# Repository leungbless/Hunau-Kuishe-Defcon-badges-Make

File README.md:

# Hunau-Kuishe-Defcon-badges-Make
想自己制作defcon的胸卡，带破解的徽章，或者带游戏的，下载的一些资料，和学习经历和自己的总结，如果做出来，会把原件，代码开源，并且分享制作经历，欢迎大家提交分支，来帮助我们改进我们的第一个徽章。

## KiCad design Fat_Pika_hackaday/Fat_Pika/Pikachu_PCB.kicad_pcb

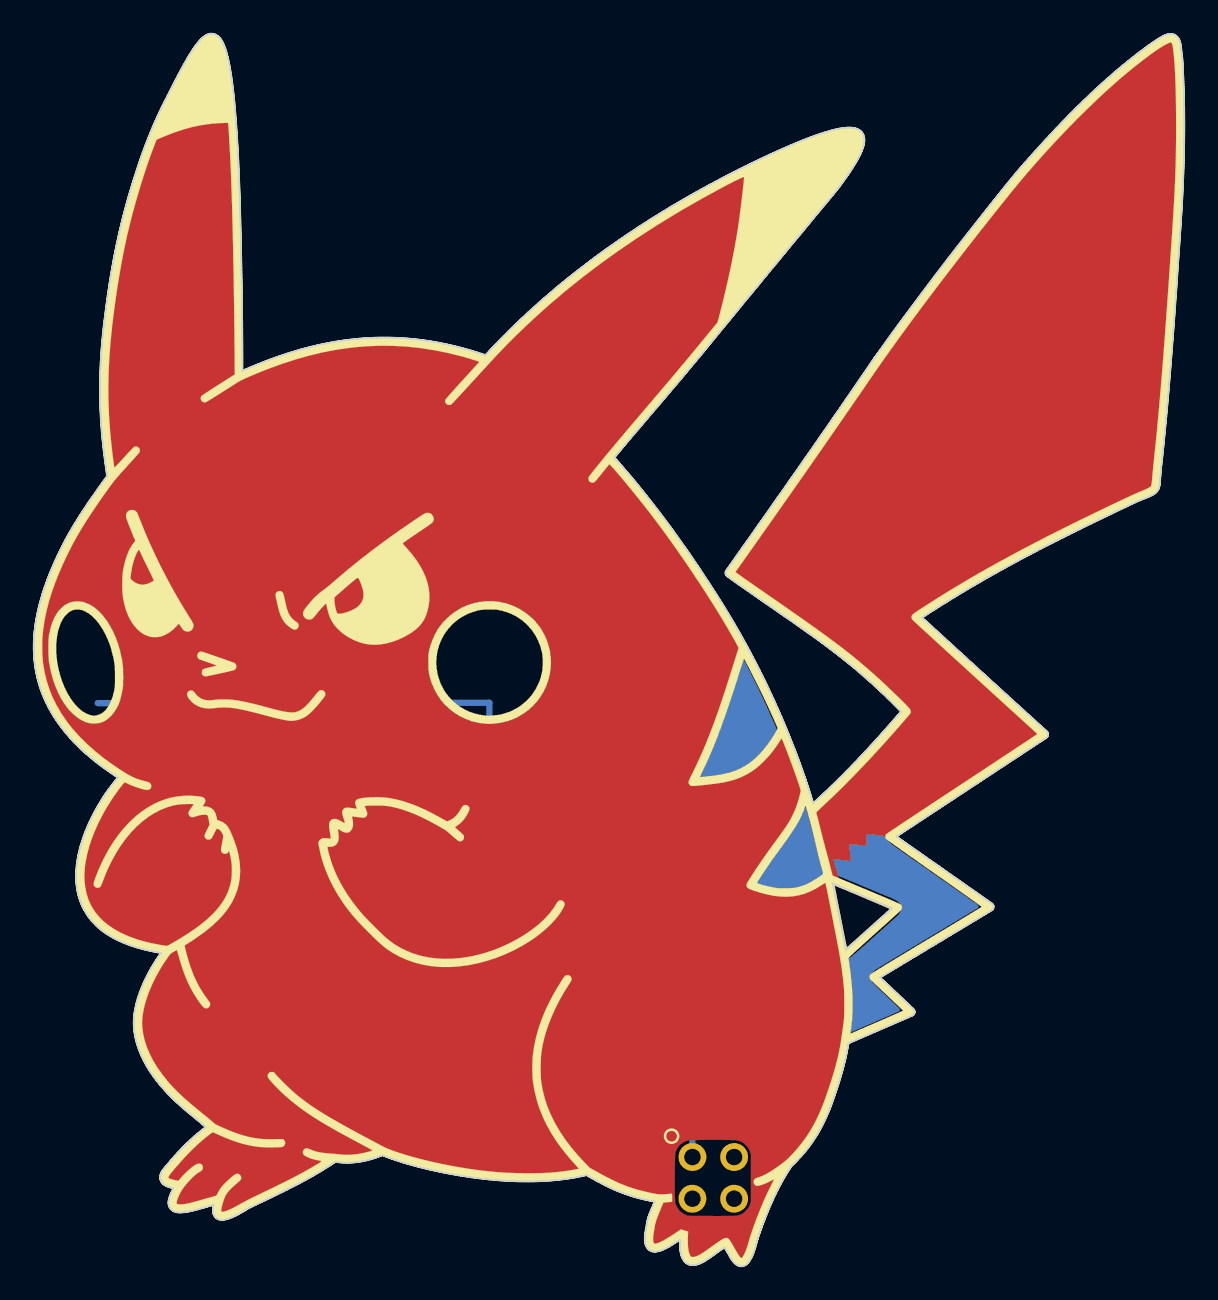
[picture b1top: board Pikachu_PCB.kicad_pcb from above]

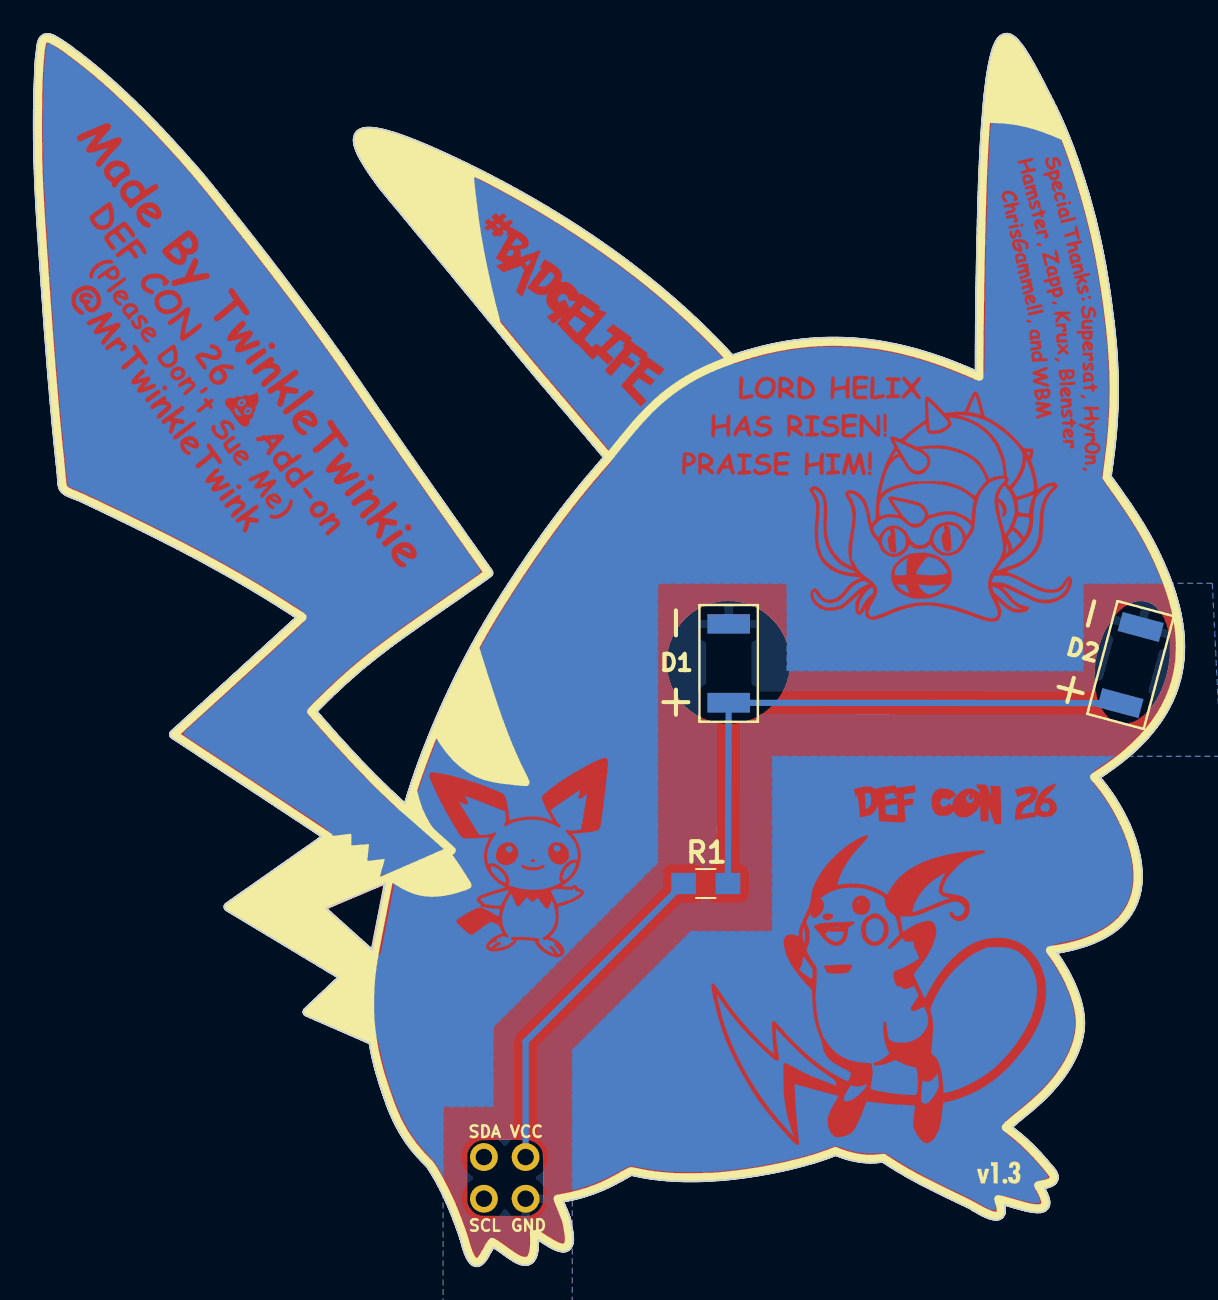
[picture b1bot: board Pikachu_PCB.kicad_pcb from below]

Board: 2 copper layers, 70.1 x 75.1 mm, 9 parts (3 on the bottom side), 3 nets.

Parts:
B.Cu: LOGO; B.Cu_g5770
B.Silk: LOGO
D1, D2: LED; LED_OSRAM_TOPLED_LxT776
F.Cu: LOGO; F.Cu_g5776
F.Mask, F.Silk: LOGO
R1: R; R_0805_HandSoldering
X1: Badgelife_shitty_connector; Badgelife-Shitty-2x2

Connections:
unnamed: D1.1, D2.1, X1.2
unnamed: D1.2, D2.2, R1.2
unnamed: R1.1, X1.1

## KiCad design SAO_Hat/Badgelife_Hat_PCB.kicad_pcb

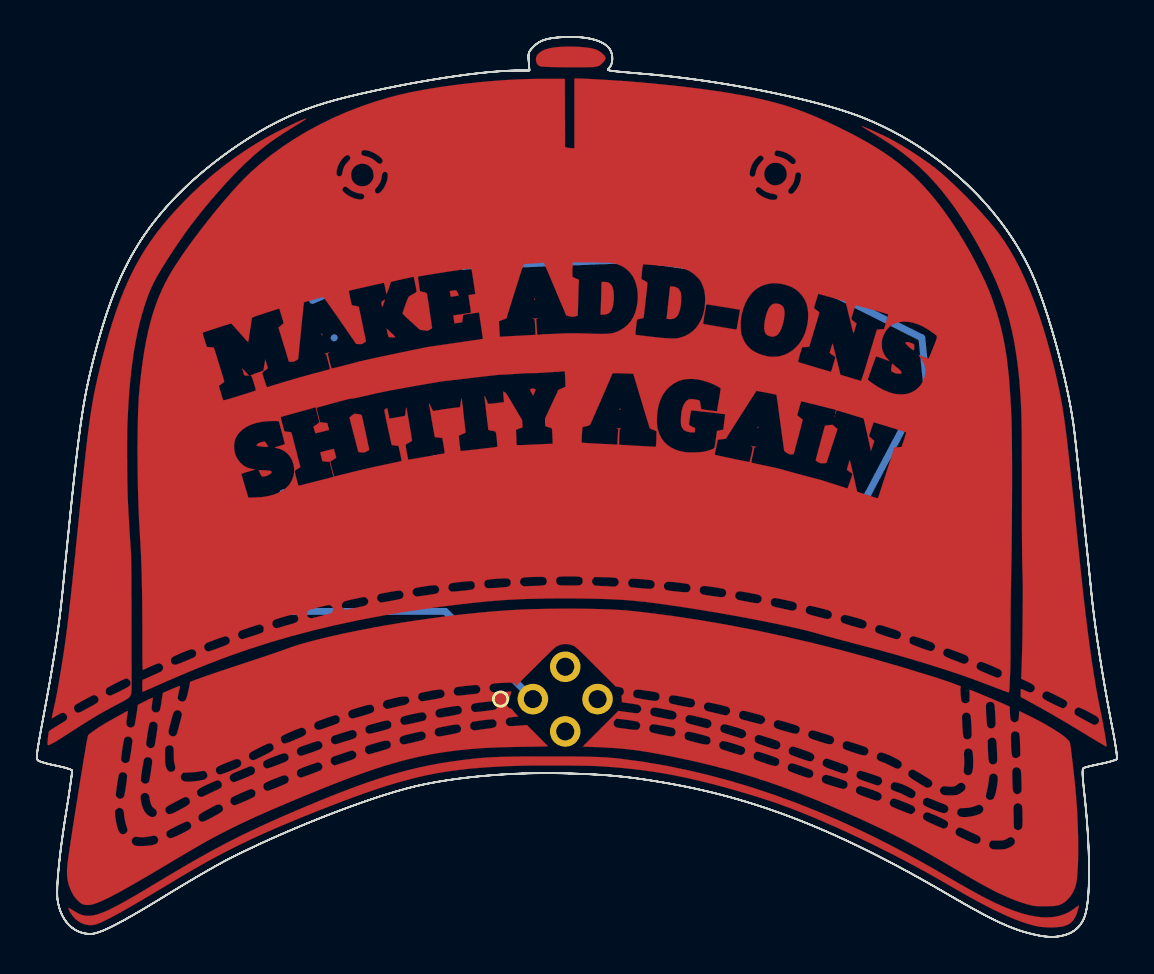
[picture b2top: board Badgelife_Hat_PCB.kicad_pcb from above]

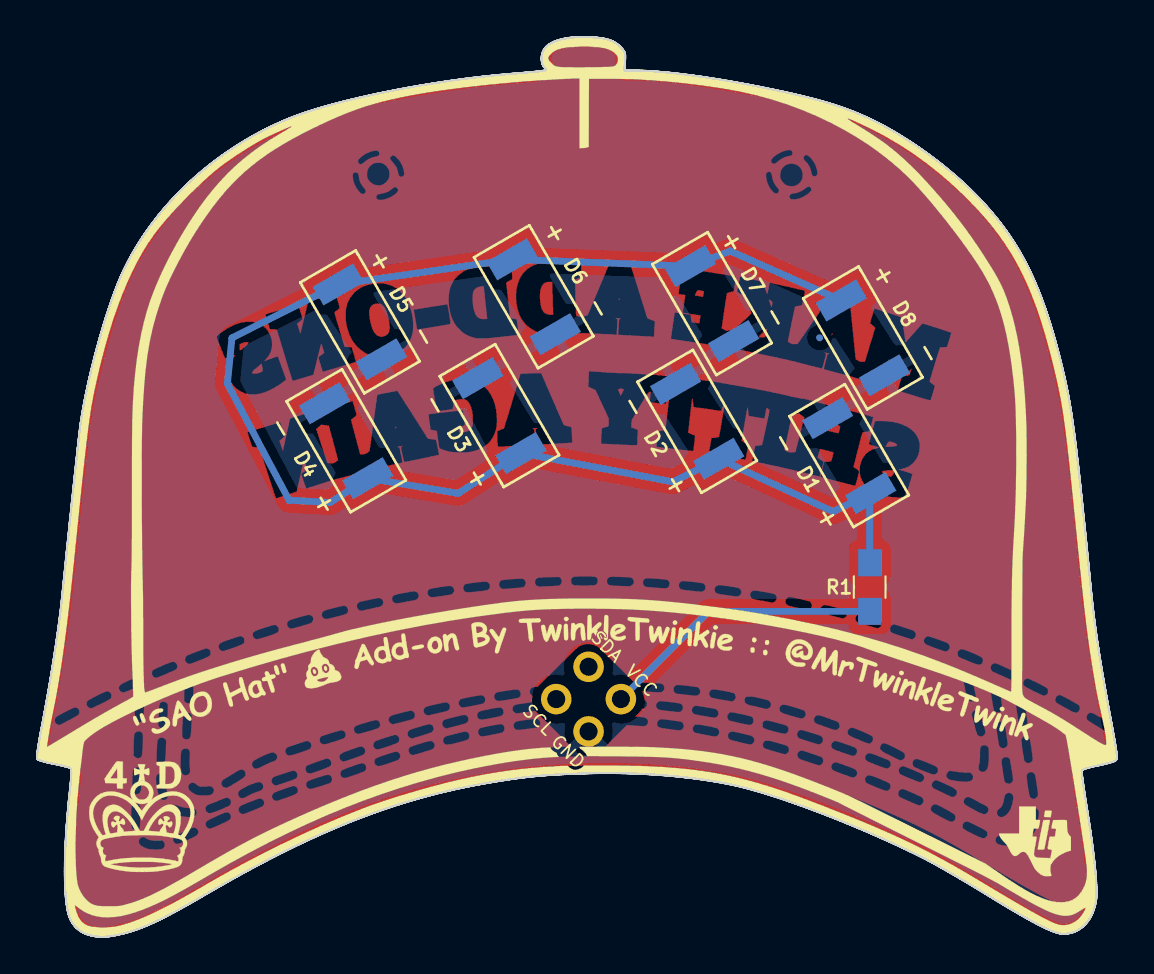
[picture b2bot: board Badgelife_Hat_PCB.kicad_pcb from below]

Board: 2 copper layers, 60.0 x 50.0 mm, 13 parts (9 on the bottom side), 3 nets.

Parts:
B.Silk: LOGO; B.Silk_g1184
D1, D2, D3, D4, D5, D6, D7, D8: LED; LED_OSRAM_TOPLED_LxT776
F.Cu: LOGO; F.Cu_g1186
F.Mask: LOGO; F.Mask_g1190
R1: 15; R_0805_HandSoldering
X1: Badgelife_shitty_connector; Badgelife-Shitty-2x2

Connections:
unnamed: D1.1, D2.1, D3.1, D4.1, D5.1, D6.1, D7.1, D8.1, X1.2
unnamed: D1.2, D2.2, D3.2, D4.2, D5.2, D6.2, D7.2, D8.2, R1.2
unnamed: R1.1, X1.1

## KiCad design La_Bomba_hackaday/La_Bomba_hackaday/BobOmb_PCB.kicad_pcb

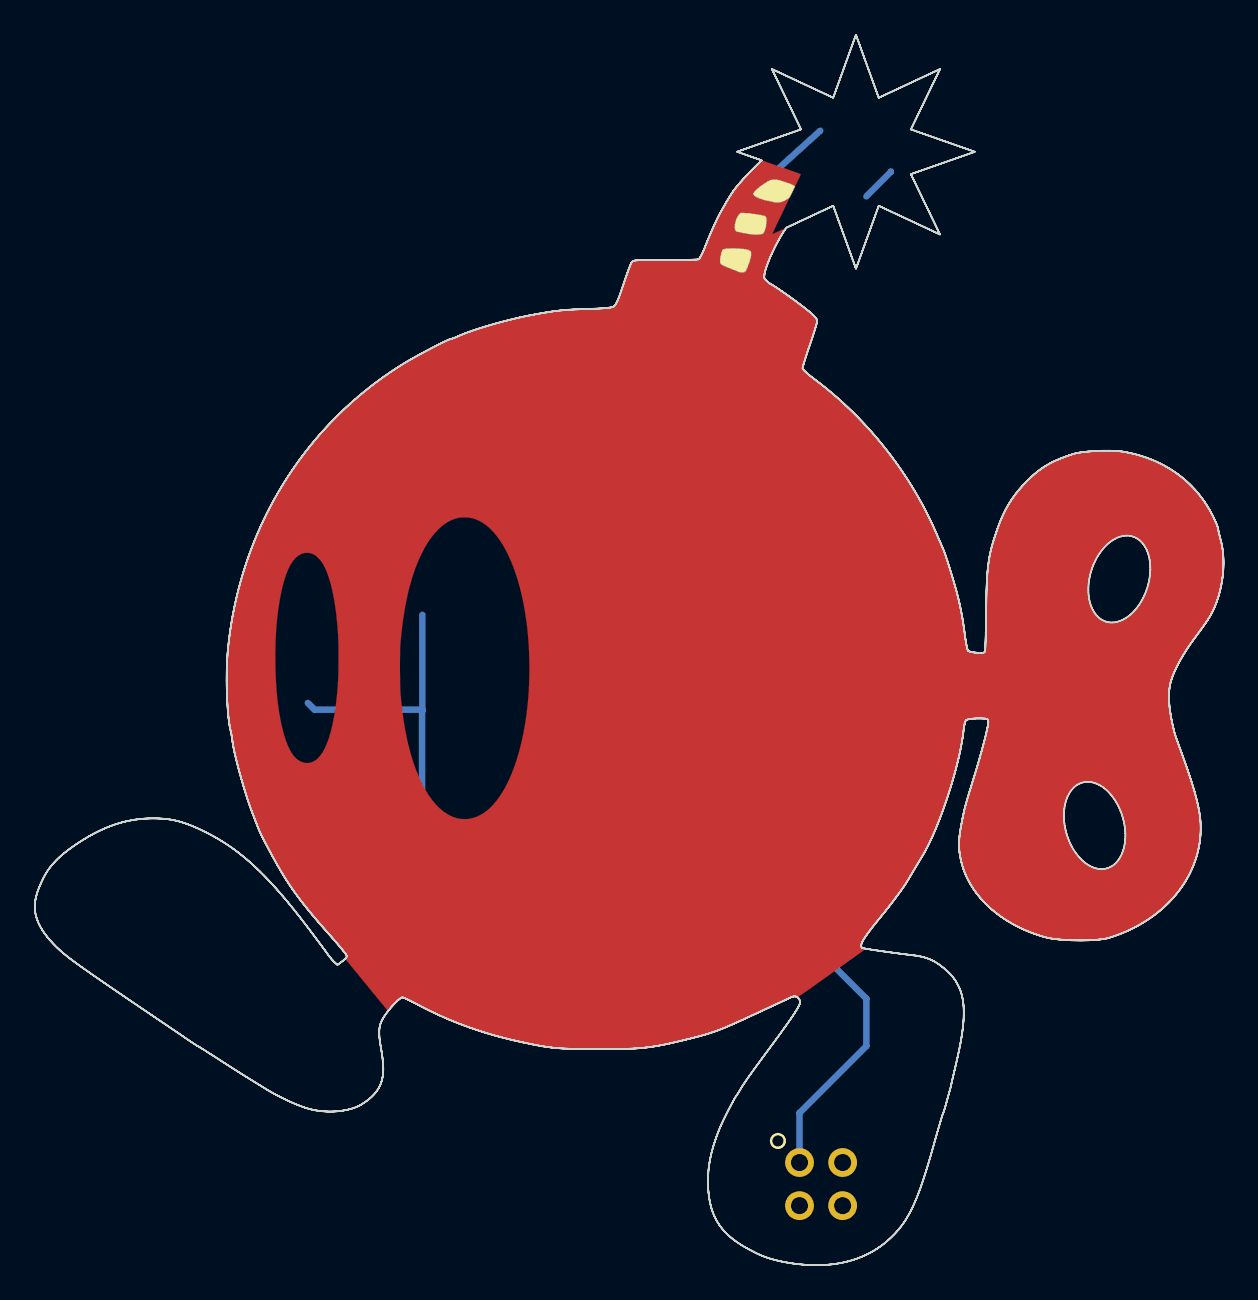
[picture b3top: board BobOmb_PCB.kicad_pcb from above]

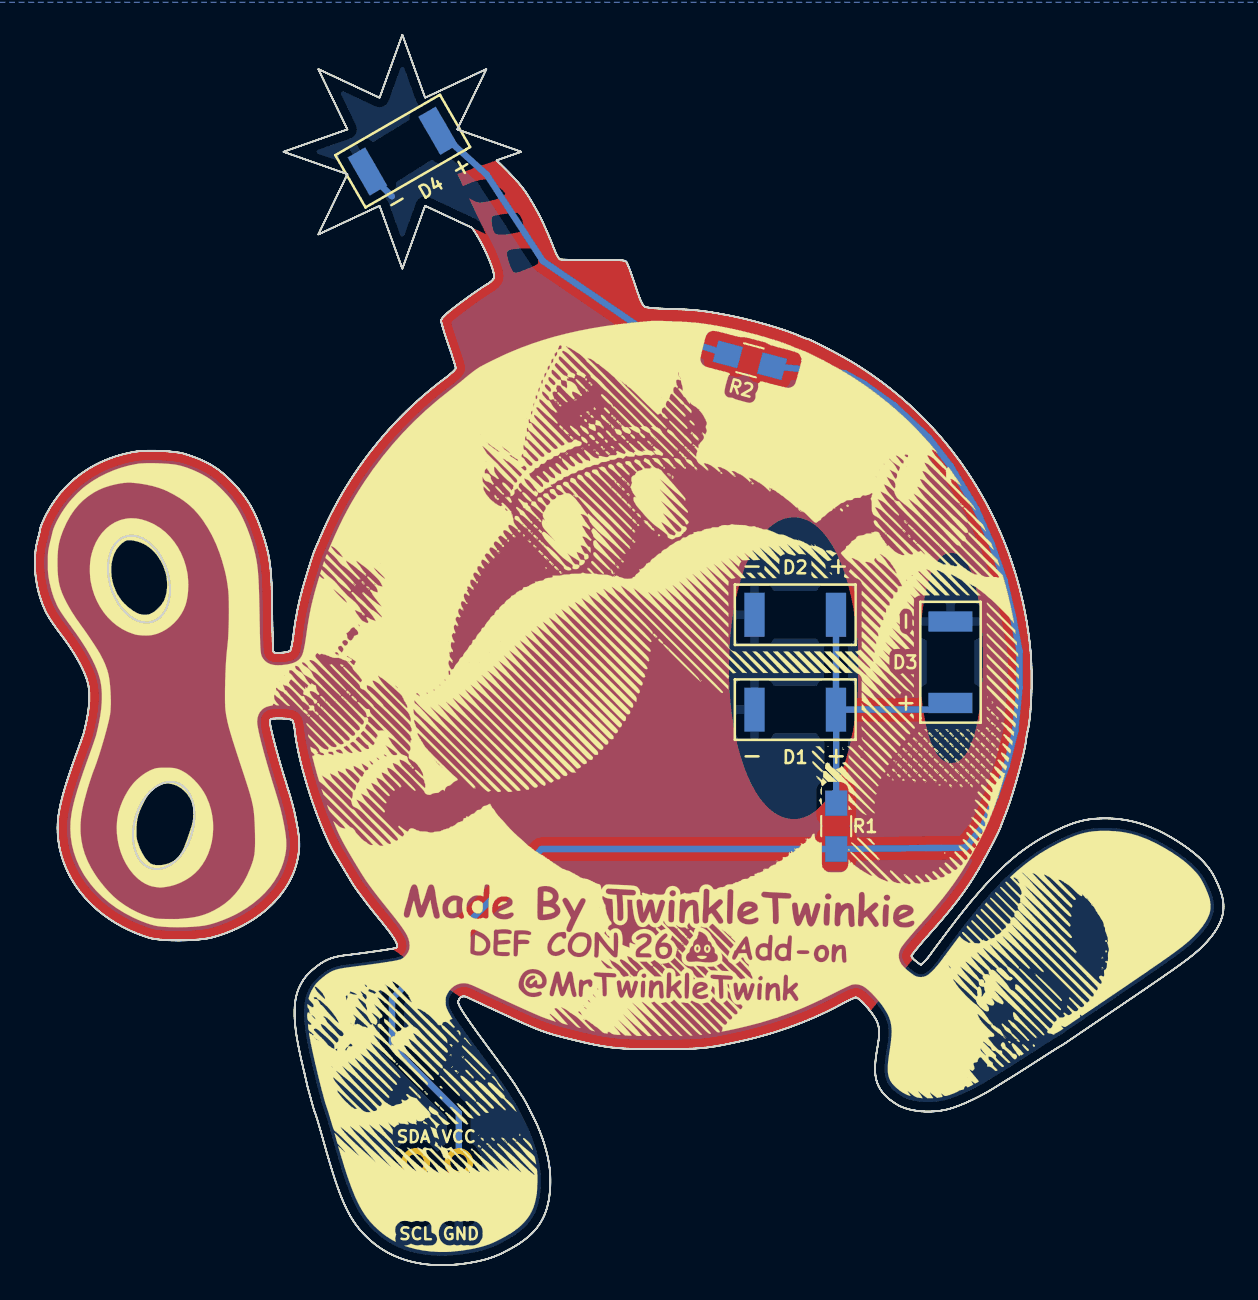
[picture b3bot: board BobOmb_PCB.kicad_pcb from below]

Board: 2 copper layers, 70.0 x 72.5 mm, 11 parts (6 on the bottom side), 4 nets.

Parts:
B.Silk: LOGO; B.Silk_g1544
D1, D2, D3, D4: LED; LED_OSRAM_TOPLED_LxT776
F.Cu, F.Silk: LOGO
F.Mask: LOGO; F.Mask_g1548
R1, R2: R; R_0805_HandSoldering
X1: Badgelife_shitty_connector; Badgelife-Shitty-2x2

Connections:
unnamed: D1.1, D2.1, D3.1, D4.1, X1.2
unnamed: D1.2, D2.2, D3.2, R1.1
unnamed: D4.2, R2.1
unnamed: R1.2, R2.2, X1.1

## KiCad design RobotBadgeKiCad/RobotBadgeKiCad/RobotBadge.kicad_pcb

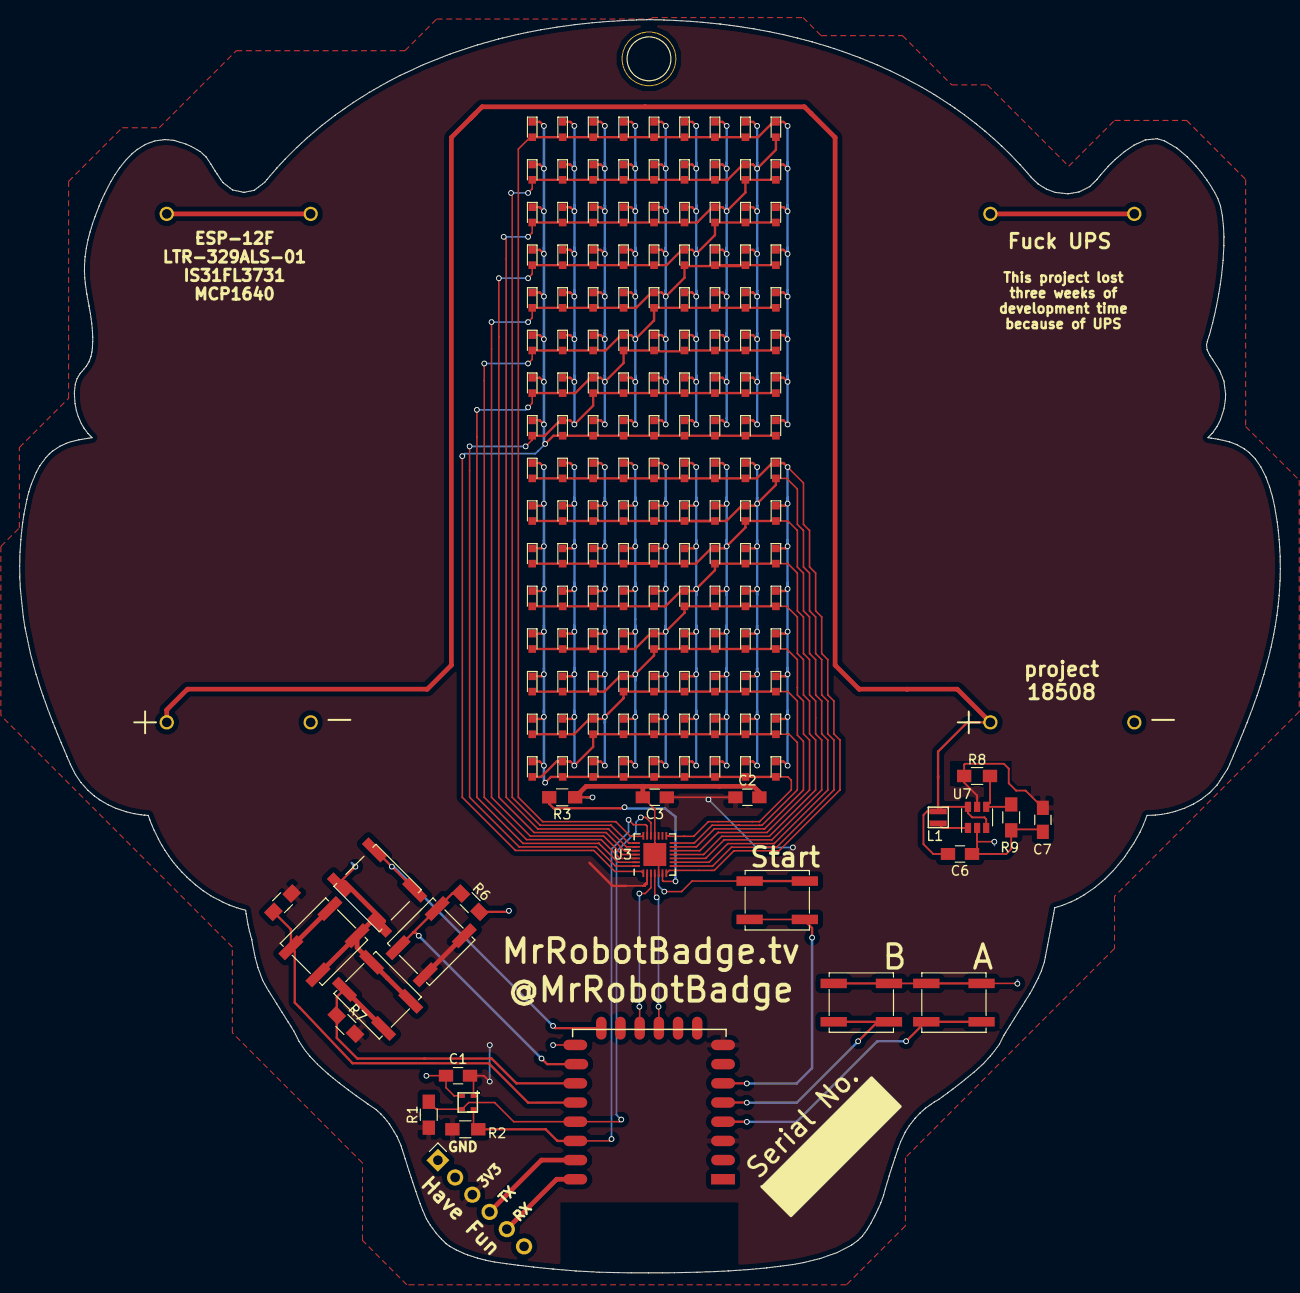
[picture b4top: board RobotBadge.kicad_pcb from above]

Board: 2 copper layers, 131.4 x 130.6 mm, 17 parts (0 on the bottom side), 8 nets.

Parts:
C1, C2: 1u; C_0805_HandSoldering
C3: 0.1u; C_0805_HandSoldering
C6: 4u7; C_0805_HandSoldering
C7: 10uF; C_0805_HandSoldering
L1: INDUCTOR_SMALL; EPL2014
R1, R2: 4k7; R_0805_HandSoldering
R3: 20k; R_0805_HandSoldering
R5, R6, R7: 10k; R_0805_HandSoldering
R8: 536k; R_0805_HandSoldering
R9: 309k; R_0805_HandSoldering
Start: SW_PUSH; SW_SPST_EVQP0
U3: IS31FL3731; QFN-28-1EP_4x4mm_Pitch0.4mm
U7: MCP1640T; SOT-23-6

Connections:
/SCL: R2.2, U3.20
/SDA: R1.2, U3.19
GND: C1.1, C2.2, C3.2, C6.1, C7.1, R3.2, R6.1, R9.1, Start.2, U3.5, U3.18, U3.29, U7.2
unnamed: C6.2, L1.1, U7.3, U7.6
unnamed: L1.2, U7.1
unnamed: R3.1, U3.6
unnamed: R8.2, R9.2, U7.4
VCC: C1.2, C2.1, C3.1, C7.2, R1.1, R2.1, R5.2, R7.2, R8.1, U3.2, U7.5
